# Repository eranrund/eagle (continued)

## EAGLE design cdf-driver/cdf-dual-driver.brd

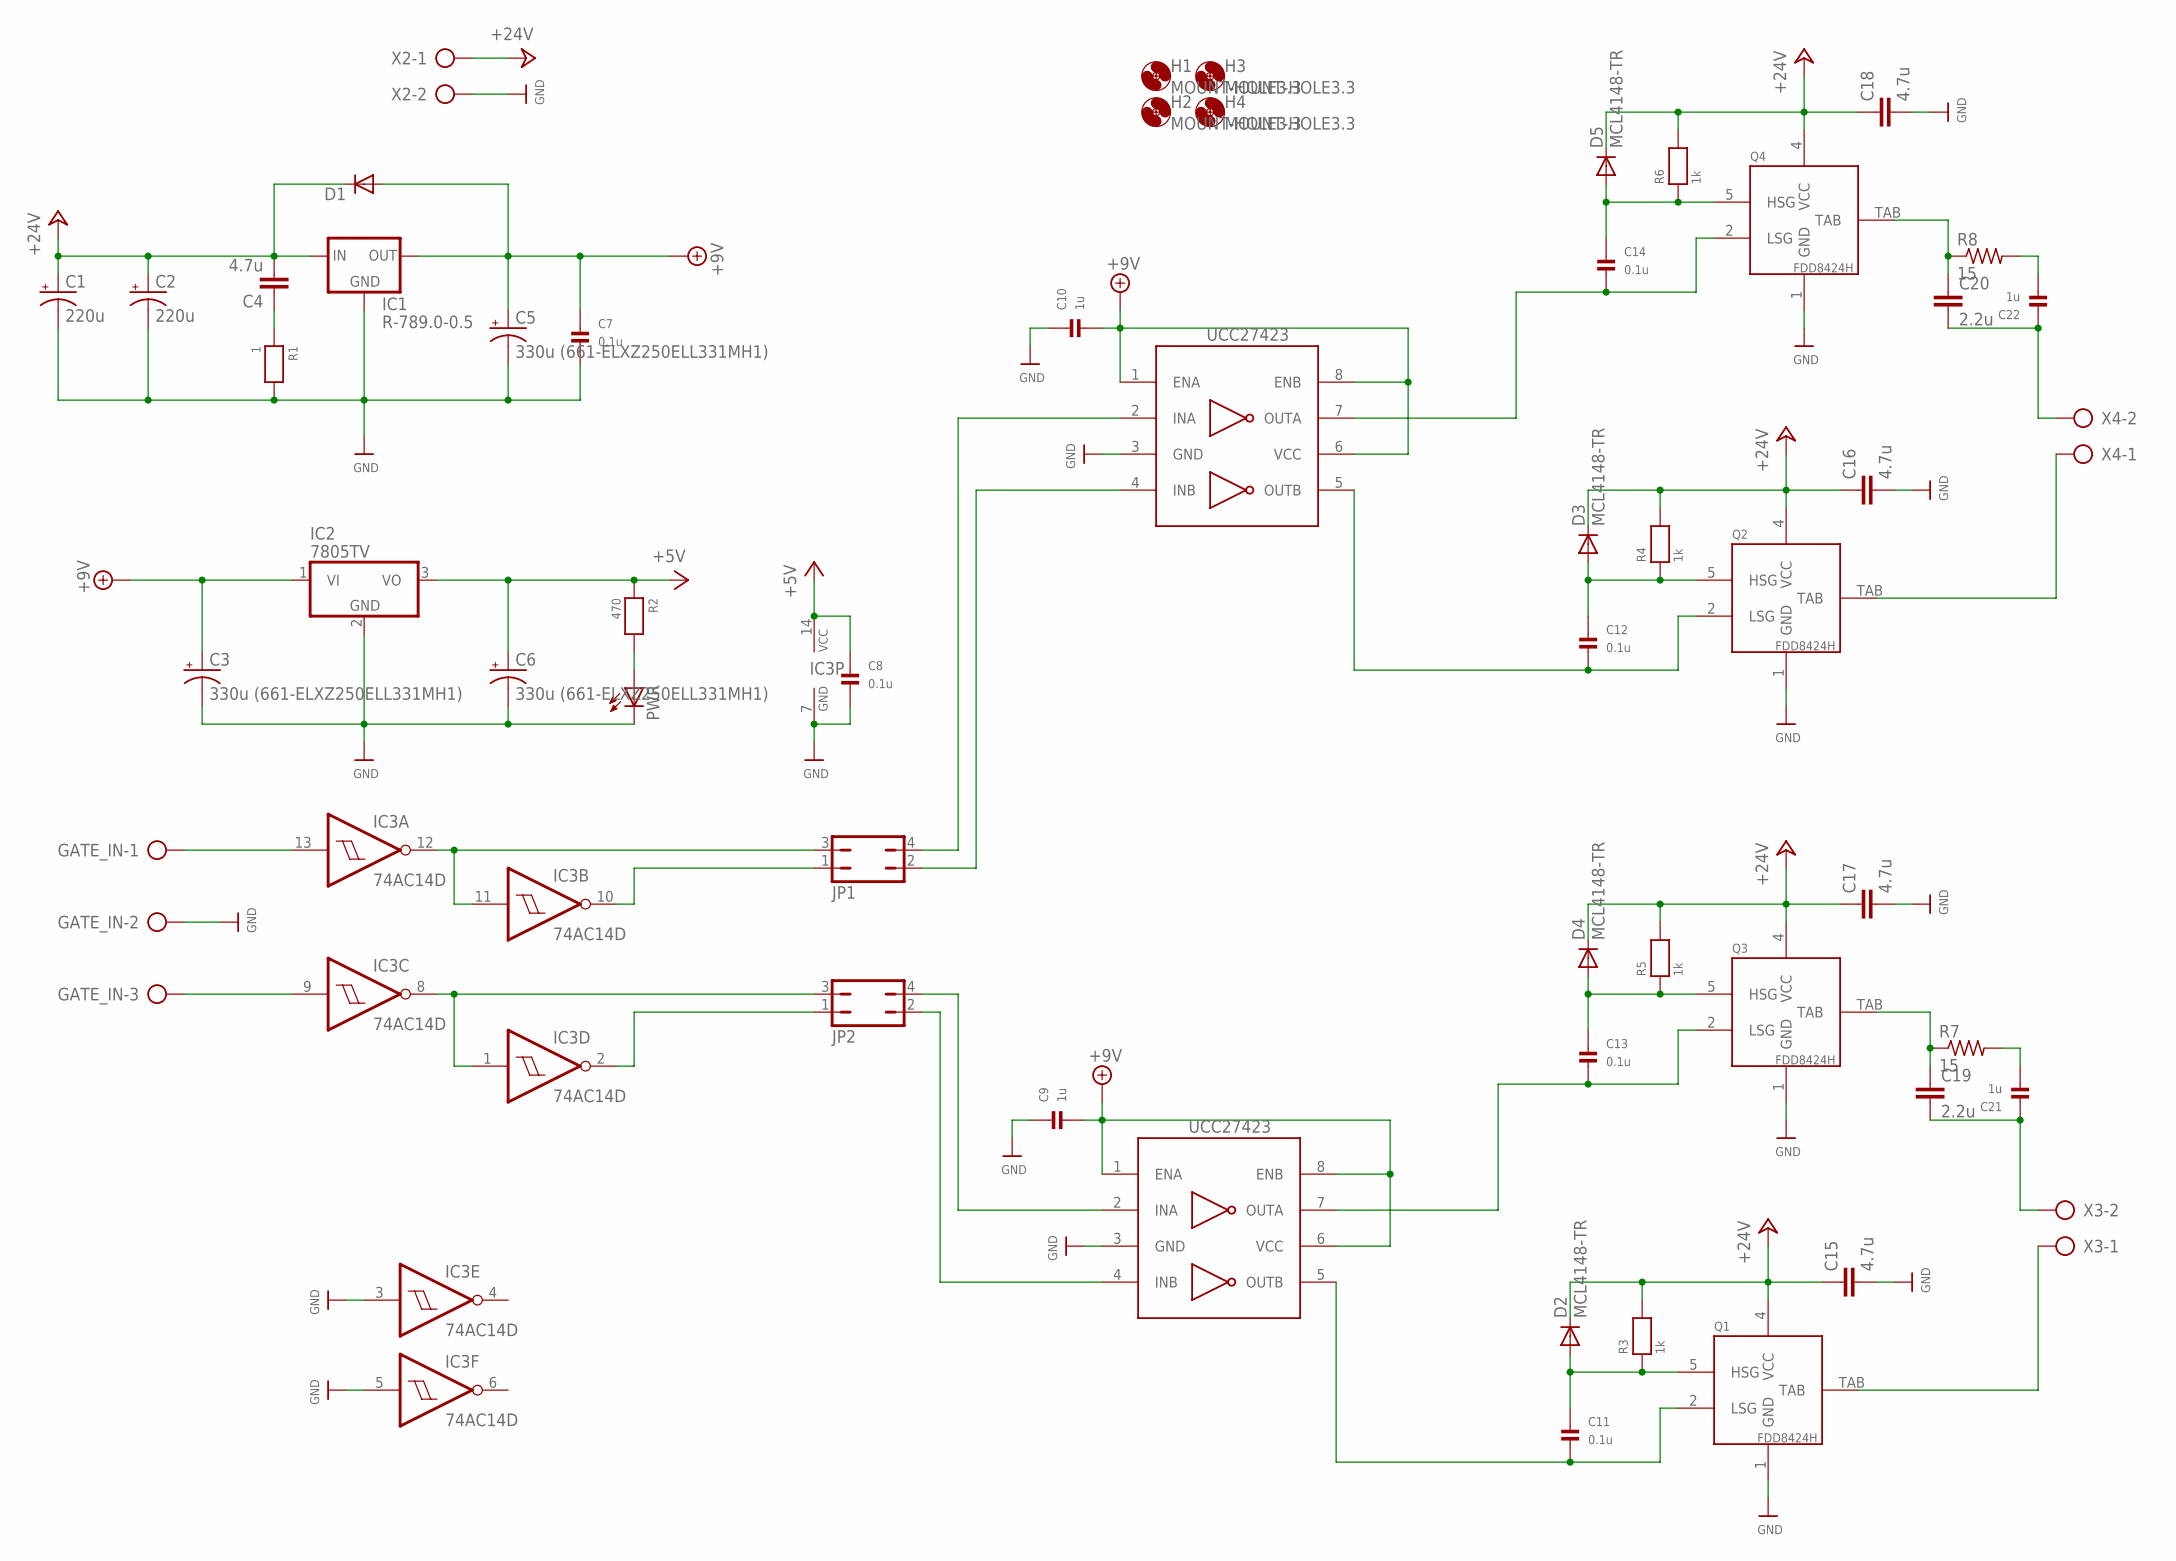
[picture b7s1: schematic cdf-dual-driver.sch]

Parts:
C1, C2: 220u; E3,5-8
C3, C5, C6: 330u (661-ELXZ250ELL331MH1); E3,5-8
C4, C15, C16, C17, C18: 4.7u; C1210
C7, C8, C11, C12, C13, C14: 0.1u; 0805
C9, C10, C21, C22: 1u; 1206
C19, C20: 2.2u; C1210
D1: DIODE-SOD123; SOD123
D2, D3, D4, D5: MCL4148-TR; MICROMELF-W
GATE_IN: AK500/3
H1, H2, H3, H4: MOUNT-HOLE3.3; 3,3
IC1: R-789.0-0.5; SIP3
IC2: 7805TV; TO220V
IC3: 74AC14D; SO14
IC4, IC5: UCC27423; SOIC8
JP1, JP2: JP2Q
PWR: LED5MM
Q1, Q2, Q3, Q4: FDD8424H; TO252-4
R1: 1; 0805
R2: 470; 0805
R3, R4, R5, R6: 1k; 0805
R7, R8: 15; R1210
X2, X3, X4: AK500/2

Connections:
+5V: C6.+, C8.1, IC2.3 (VO), IC3.14 (VCC), R2.1
+9V: C3.+, C5.+, C7.1, C9.2, C10.2, D1.A, IC1.3 (OUT), IC2.1 (VI), IC4.1 (ENA), IC4.6 (VCC), IC4.8 (ENB), IC5.1 (ENA), IC5.6 (VCC), IC5.8 (ENB)
+24V: C1.+, C2.+, C4.2, C15.1, C16.1, C17.1, C18.1, D1.C, D2.C, D3.C, D4.C, D5.C, IC1.1 (IN), Q1.4 (VCC), Q2.4 (VCC), Q3.4 (VCC), Q4.4 (VCC), R3.2, R4.2, R5.2, R6.2, X2.1
GND: C1.-, C2.-, C3.-, C5.-, C6.-, C7.2, C8.2, C9.1, C10.1, C15.2, C16.2, C17.2, C18.2, GATE_IN.2, IC1.2 (GND), IC2.2 (GND), IC3.3 (I), IC3.5 (I), IC3.7 (GND), IC4.3 (GND), IC5.3 (GND), PWR.K (C), Q1.1 (GND), Q2.1 (GND), Q3.1 (GND), Q4.1 (GND), R1.2, X2.2
unnamed: C13.2, IC4.7 (OUTA), Q3.2 (LSG)
unnamed: C13.1, D4.A, Q3.5 (HSG), R5.1
unnamed: C14.2, IC5.7 (OUTA), Q4.2 (LSG)
unnamed: C14.1, D5.A, Q4.5 (HSG), R6.1
unnamed: C20.1, Q4.TAB, R8.1
unnamed: C22.2, R8.2
unnamed: C20.2, C22.1, X4.2
unnamed: C12.2, IC5.5 (OUTB), Q2.2 (LSG)
unnamed: C12.1, D3.A, Q2.5 (HSG), R4.1
unnamed: Q2.TAB, X4.1
unnamed: C4.1, R1.1
unnamed: C19.1, Q3.TAB, R7.1
unnamed: C21.2, R7.2
unnamed: C19.2, C21.1, X3.2
unnamed: C11.2, IC4.5 (OUTB), Q1.2 (LSG)
unnamed: C11.1, D2.A, Q1.5 (HSG), R3.1
unnamed: Q1.TAB, X3.1
unnamed: PWR.A, R2.2
unnamed: IC5.2 (INA), JP1.4
unnamed: IC5.4 (INB), JP1.2
unnamed: IC4.2 (INA), JP2.4
unnamed: IC4.4 (INB), JP2.2
unnamed: IC3.11 (I), IC3.12 (O), JP1.3
unnamed: GATE_IN.1, IC3.13 (I)
unnamed: GATE_IN.3, IC3.9 (I)
unnamed: IC3.10 (O), JP1.1
unnamed: IC3.1 (I), IC3.8 (O), JP2.3
unnamed: IC3.2 (O), JP2.1

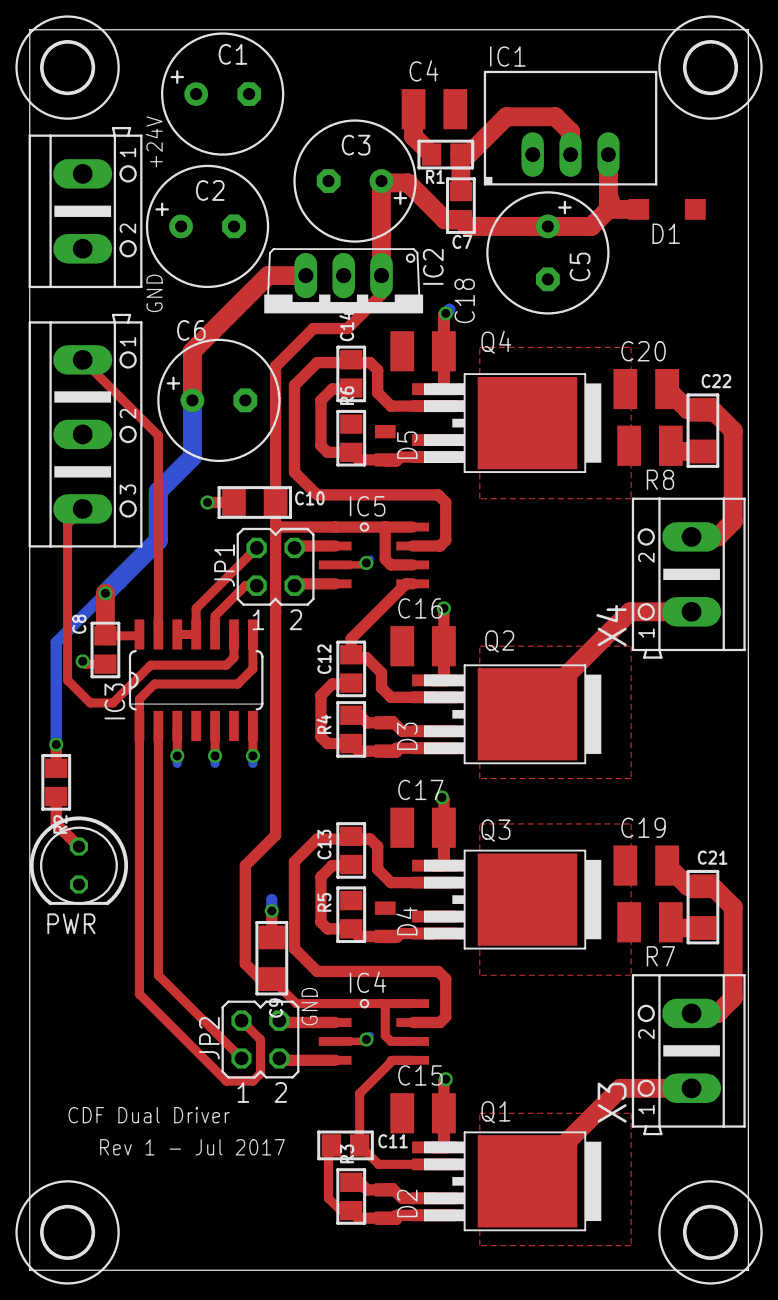
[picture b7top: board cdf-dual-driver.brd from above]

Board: 2 copper layers, 48.3 x 83.3 mm, 55 parts (0 on the bottom side), 32 nets.

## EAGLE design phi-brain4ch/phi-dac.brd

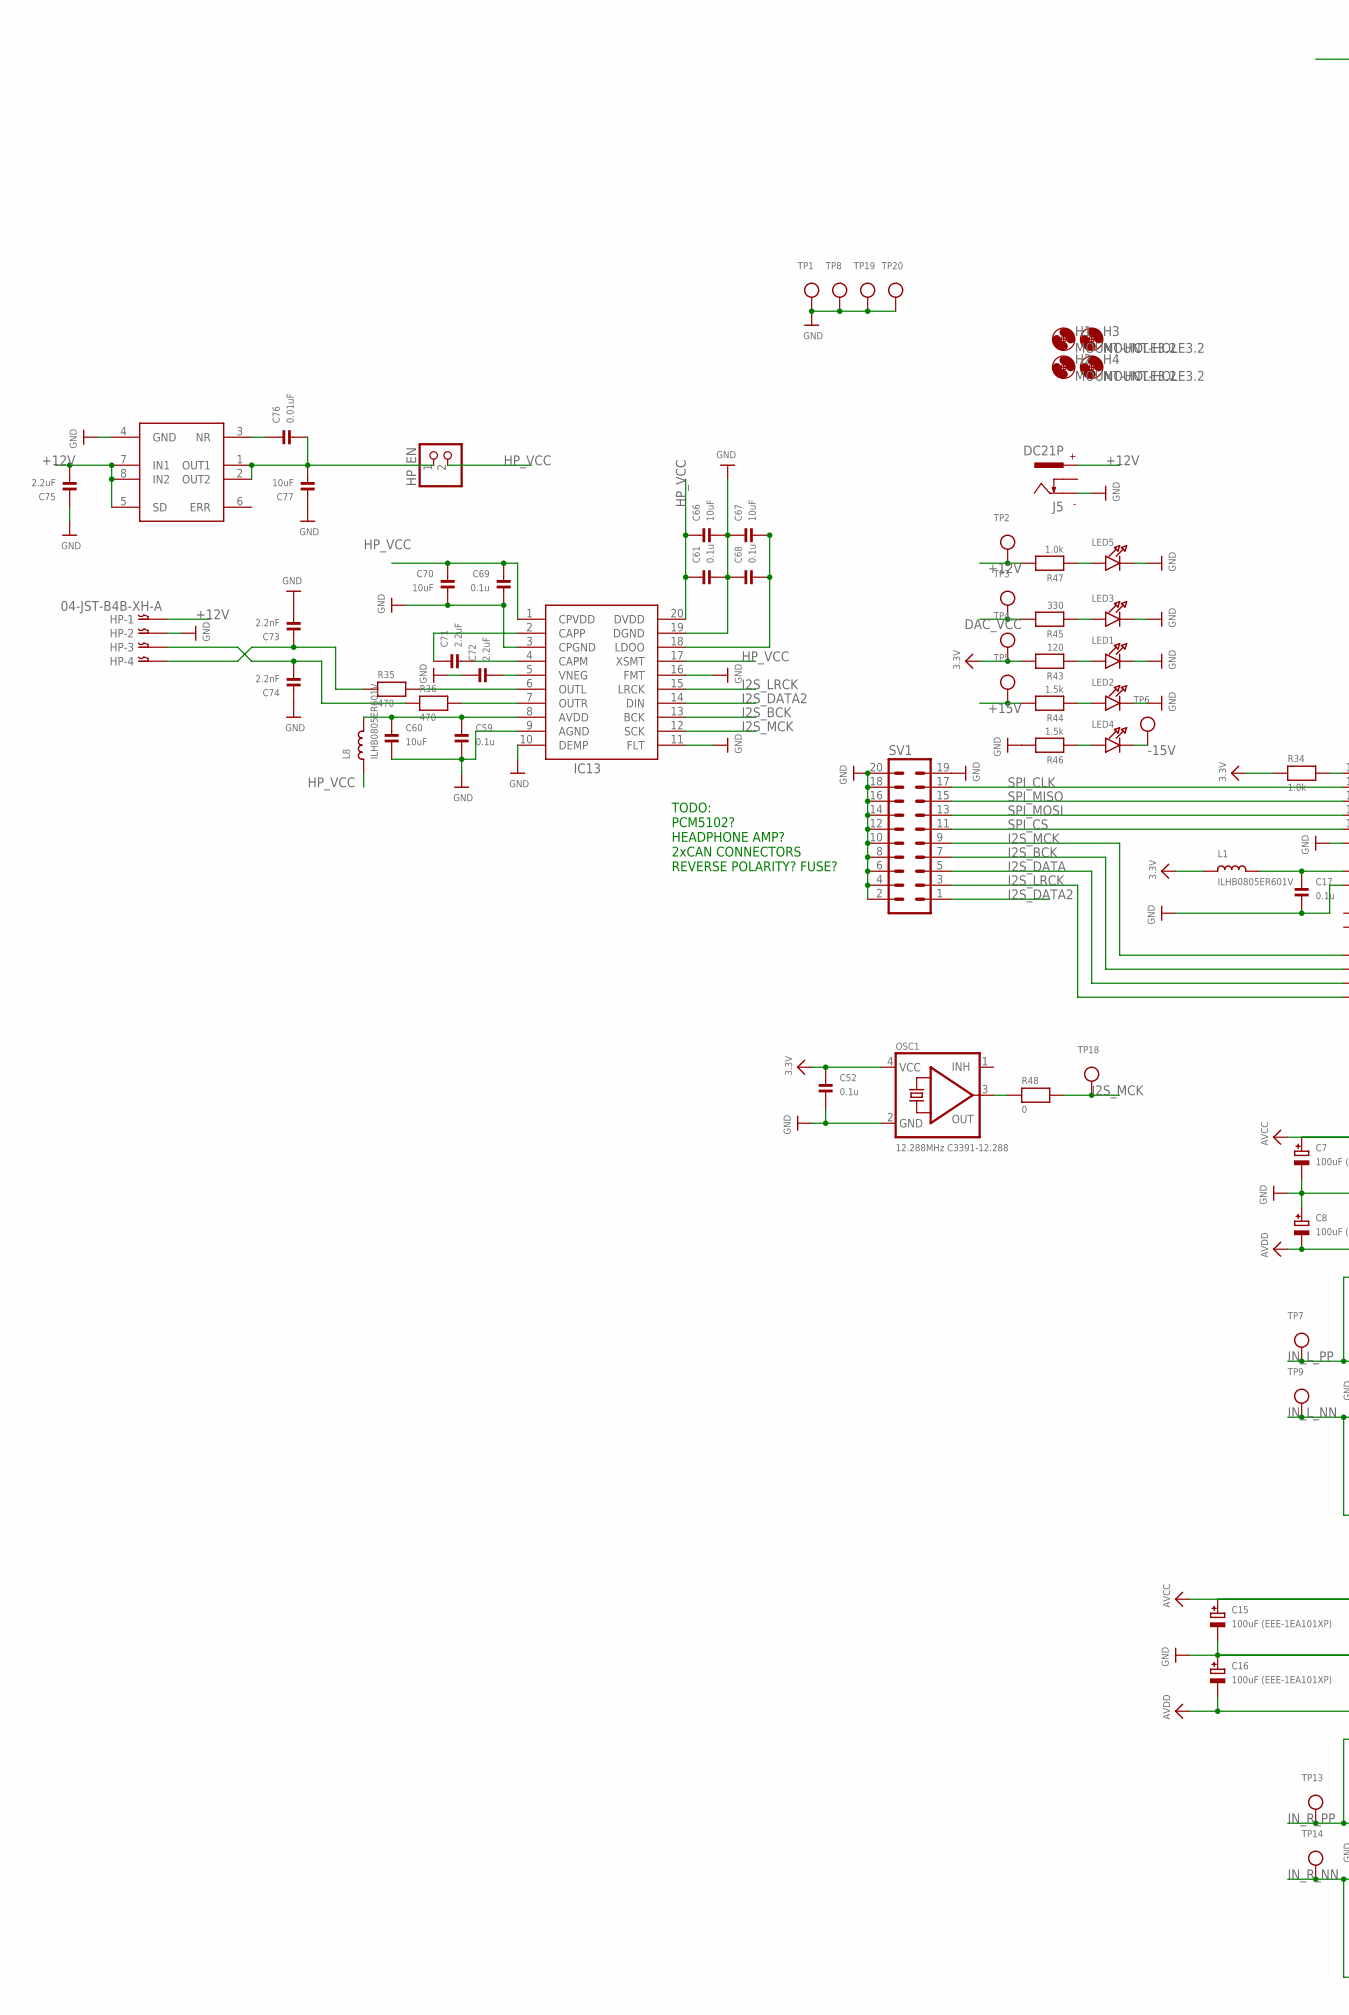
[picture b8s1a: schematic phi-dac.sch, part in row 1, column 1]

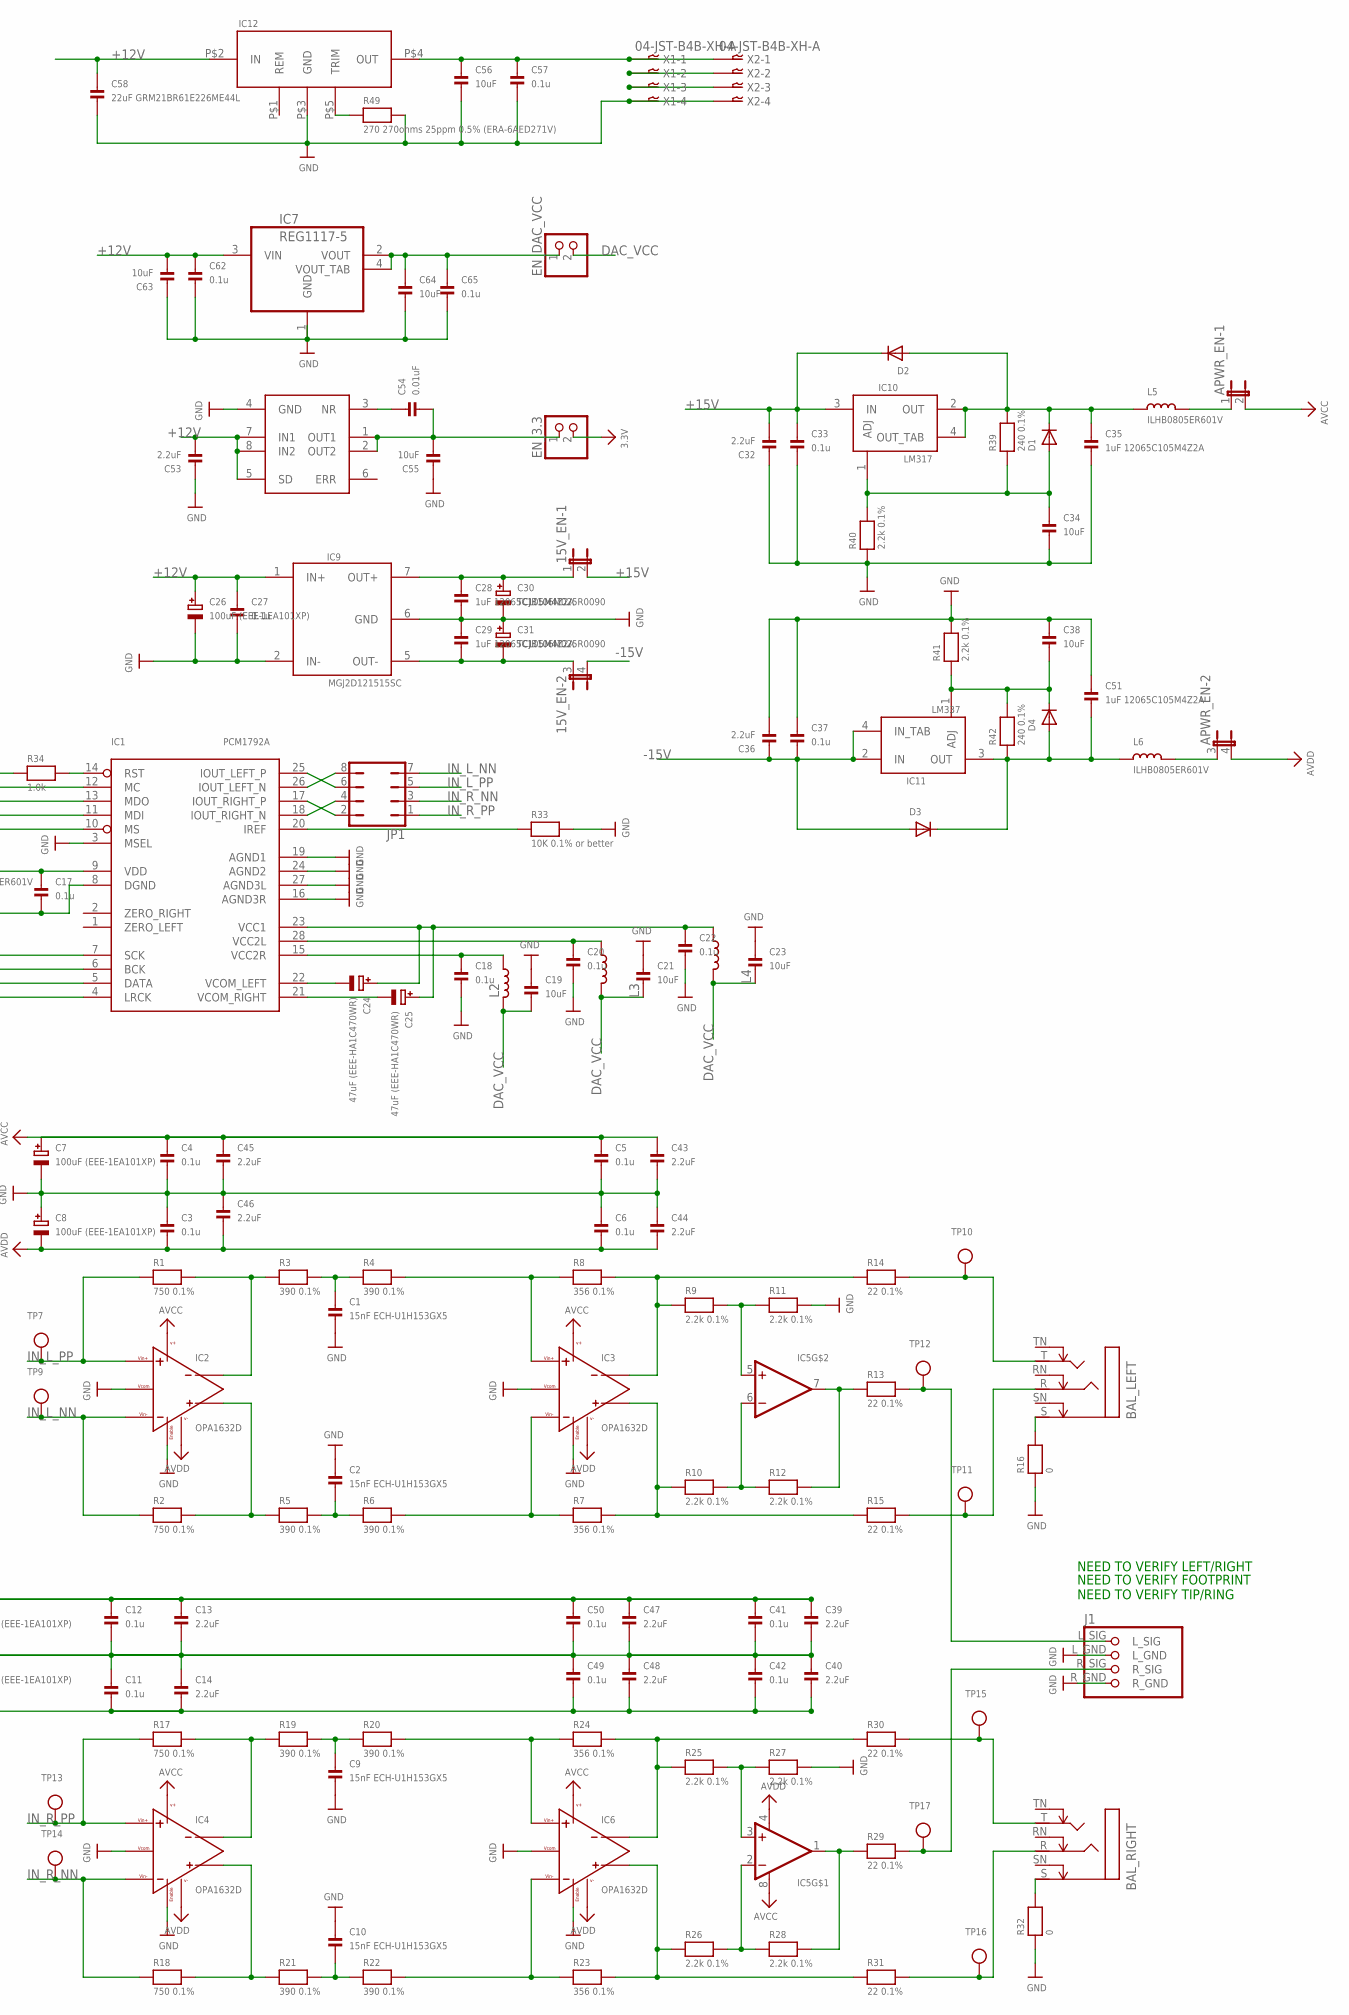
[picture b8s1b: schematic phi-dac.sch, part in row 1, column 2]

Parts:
15V_EN: JP2QE; JP2Q
APWR_EN: JP2QE; JP2Q
BAL_LEFT: STEREOSW; NMJ6HCD2
BAL_RIGHT: STEREOSW; NMJ6HCD2
C1, C2, C9, C10: 15nF ECH-U1H153GX5; 1210
C3, C4, C5, C6, C11, C12, C17, C18, C20, C22, C27, C33, C37, C41, C42, C49, C50, C52, C57, C59, C61, C62, C65, C68, C69: 0.1u; 0603
C7, C8, C15, C16, C26: 100uF (EEE-1EA101XP); PANASONIC_D
C13, C14, C32, C36, C39, C40, C43, C44, C45, C46, C47, C48, C53, C71, C72, C75: 2.2uF; _0805
C19, C21, C23, C34, C38, C55, C56, C60, C63, C64, C66, C67, C70, C77: 10uF; 0805
C24, C25: 47uF (EEE-HA1C470WR); PANASONIC_C
C28, C29, C35, C51: 1uF 12065C105M4Z2A; 1206
C30, C31: TCJB106M025R0090; 1210POL
C54, C76: 0.01uF; 0603
C58: 22uF GRM21BR61E226ME44L; _0805
C73, C74: 2.2nF; _0805
D1, D2, D3, D4: DIODESOD-123; SOD-123
EN_3.3: HEADER-1X2; 1X02_OVAL
EN_DAC_VCC: HEADER-1X2; 1X02_OVAL
H1, H2, H3, H4: MOUNT-HOLE3.2; 3,2
HP: 04-JST-B4B-XH-A; B4B-XH
HP_EN: HEADER-1X2; 1X02_OVAL
IC1: PCM1792A; SSOP28
IC2, IC3, IC4, IC6: OPA1632D; SO08
IC5: LM4562; SOIC8_150MIL
IC7: REG1117-5; SOT223
IC8, IC14: ADP3301ARZ-3.3; SO08
IC9: MGJ2D121515SC; MURATA-MGJ2
IC10: LM317; SOT223
IC11: LM337; SOT223
IC12: MURATA_OKR-T/10-W12-C
IC13: PCM5102; TSSOP20
J1: CUI-RCJ-2123
J5: DC21P; CUI-PJ-102AH
JP1: JP4Q
L1, L2, L3, L4, L5, L6, L8: ILHB0805ER601V; _0805
LED1, LED2, LED3, LED4, LED5: LED0805; CHIPLED_0805
OSC1: 12.288MHz C3391-12.288; OSC_7X5MM
R1, R2, R17, R18: 750 0.1%; _0805
R3, R4, R5, R6, R19, R20, R21, R22: 390 0.1%; _0805
R7, R8, R23, R24: 356 0.1%; _0805
R9, R10, R11, R12, R25, R26, R27, R28, R40, R41: 2.2k 0.1%; _0805
R13, R14, R15, R29, R30, R31: 22 0.1%; _0805
R16, R32, R48: 0; _0805
R33: 10K 0.1% or better; _0805
R34, R47: 1.0k; _0805
R35, R36: 470; _0805
R39, R42: 240 0.1%; _0805
R43: 120; _0805
R44, R46: 1.5k; _0805
R45: 330; _0805
R49: 270 270ohms 25ppm 0.5% (ERA-6AED271V); _0805
SV1: ML20
TP1, TP2, TP3, TP4, TP5, TP6, TP7, TP8, TP9, TP10, TP11, TP12, TP13, TP14, TP15, TP16, TP17, TP18, TP19, TP20: TESTPOINT0.1"; 1X01_ROUND
X1, X2: 04-JST-B4B-XH-A; B4B-XH

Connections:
3.3V: C52.1, EN_3.3.2, L1.1, OSC1.4 (VCC), R34.1, R43.2, TP4.1
+12V: C26.+, C27.1, C53.2, C58.1, C62.1, C63.2, C75.2, HP.P$1, IC7.3 (VIN), IC8.5 (SD), IC8.7 (IN1), IC8.8 (IN2), IC9.1 (IN+), IC12.P$2 (IN), IC14.5 (SD), IC14.7 (IN1), IC14.8 (IN2), J5.+, R47.2, TP2.1
+15V: 15V_EN.2, C32.2, C33.1, D2.C, IC10.3 (IN), R44.2, TP5.1
-15V: 15V_EN.4 (2), C36.1, C37.2, D3.A, IC11.2 (IN), IC11.4 (IN_TAB), LED4.C, TP6.1
AVCC: APWR_EN.2, C4.1, C5.1, C7.+, C12.1, C13.1, C15.+, C39.1, C41.1, C43.1, C45.1, C47.1, C50.1, IC2.3 (V+), IC3.3 (V+), IC4.3 (V+), IC5.8 (V+), IC6.3 (V+)
AVDD: APWR_EN.4 (2), C3.2, C6.2, C8.-, C11.2, C14.2, C16.-, C40.2, C42.2, C44.2, C46.2, C48.2, C49.2, IC2.6 (V-), IC3.6 (V-), IC4.6 (V-), IC5.4 (V-), IC6.6 (V-)
CAN_H: X1.P$3, X2.P$3
CAN_L: X1.P$2, X2.P$2
DAC_VCC: C19.2, C21.2, C23.2, EN_DAC_VCC.2, L2.2, L3.2, L4.2, R45.2, TP3.1
GND: C1.2, C2.1, C3.1, C4.2, C5.2, C6.1, C7.-, C8.+, C9.2, C10.1, C11.1, C12.2, C13.2, C14.1, C15.-, C16.+, C17.2, C18.2, C19.1, C20.2, C21.1, C22.2, C23.1, C26.-, C27.2, C28.2, C29.1, C30.2- (-), C31.1+ (+), C32.1, C33.2, C34.2, C35.2, C36.2, C37.1, C38.1, C39.2, C40.1, C41.2, C42.1, C43.2, C44.1, C45.2, C46.1, C47.2, C48.1, C49.1, C50.2, C51.1, C52.2, C53.1, C55.1, C56.2, C57.2, C58.2, C59.2, C60.2, C61.2, C62.2, C63.1, C64.2, C65.2, C66.2, C67.1, C68.1, C69.2, C70.2, C72.1, C73.2, C74.1, C75.1, C77.1, HP.P$2, IC1.3 (MSEL), IC1.8 (DGND), IC1.16 (AGND3R), IC1.19 (AGND1), IC1.24 (AGND2), IC1.27 (AGND3L), IC2.2 (VCOM), IC2.7 (ENABLE), IC3.2 (VCOM), IC3.7 (ENABLE), IC4.2 (VCOM), IC4.7 (ENABLE), IC6.2 (VCOM), IC6.7 (ENABLE), IC7.1 (GND), IC8.4 (GND), IC9.2 (IN-), IC9.6 (GND), IC12.P$3 (GND), IC13.3 (CPGND), IC13.9 (AGND), IC13.10 (DEMP), IC13.11 (FLT), IC13.16 (FMT), IC13.19 (DGND), IC14.4 (GND), J1.L_GND, J1.R_GND, J5.-, LED1.C, LED2.C, LED3.C, LED5.C, OSC1.2 (GND), R11.2, R16.1, R27.2, R32.1, R33.2, R40.1, R41.2, R46.2, R49.2, SV1.2, SV1.4, SV1.6, SV1.8, SV1.10, SV1.12, SV1.14, SV1.16, SV1.18, SV1.19, SV1.20, TP1.1, TP8.1, TP19.1, TP20.1, X1.P$4, X2.P$4
HP_L_OUT: C73.1, HP.P$4, R35.1
HP_R_OUT: C74.2, HP.P$3, R36.1
HP_VCC: C61.1, C66.1, C69.1, C70.1, HP_EN.2, IC13.1 (CPVDD), IC13.17 (XSMT), IC13.20 (DVDD), L8.1
I2S_BCK: IC1.6 (BCK), IC13.13 (BCK), SV1.7
I2S_DATA: IC1.5 (DATA), SV1.5
I2S_DATA2: IC13.14 (DIN), SV1.1
I2S_LRCK: IC1.4 (LRCK), IC13.15 (LRCK), SV1.3
I2S_MCK: IC1.7 (SCK), IC13.12 (SCK), R48.2, SV1.9, TP18.1
IN_L_NN: IC2.1 (VIN-), JP1.7, R2.1, TP9.1
IN_L_PP: IC2.8 (VIN+), JP1.5, R1.1, TP7.1
IN_R_NN: IC4.1 (VIN-), JP1.3, R18.1, TP14.1
IN_R_PP: IC4.8 (VIN+), JP1.1, R17.1, TP13.1
unnamed: IC2.5 (VOUT-), R1.2, R3.1
unnamed: IC2.4 (VOUT+), R2.2, R5.1
unnamed: C1.1, R3.2, R4.1
unnamed: C2.2, R5.2, R6.1
unnamed: IC3.8 (VIN+), R4.2, R8.1
unnamed: IC3.1 (VIN-), R6.2, R7.1
unnamed: IC1.17 (IOUT_RIGHT_P), JP1.2
unnamed: IC1.18 (IOUT_RIGHT_N), JP1.4
unnamed: IC5.5 (+IN), R9.2, R11.1
unnamed: IC5.6 (-IN), R10.2, R12.1
unnamed: IC5.7 (OUT), R12.2, R13.1
unnamed: J1.L_SIG, R13.2, TP12.1
unnamed: BAL_LEFT.S, R16.2
unnamed: BAL_LEFT.T, R14.2, TP10.1
unnamed: BAL_LEFT.R, R15.2, TP11.1
unnamed: IC4.5 (VOUT-), R17.2, R19.1
unnamed: IC4.4 (VOUT+), R18.2, R21.1
unnamed: C9.1, R19.2, R20.1
unnamed: C10.2, R21.2, R22.1
unnamed: IC6.8 (VIN+), R20.2, R24.1
unnamed: IC6.1 (VIN-), R22.2, R23.1
unnamed: IC1.26 (IOUT_LEFT_N), JP1.8
unnamed: IC1.25 (IOUT_LEFT_P), JP1.6
unnamed: IC5.3 (+IN), R25.2, R27.1
unnamed: IC5.2 (-IN), R26.2, R28.1
unnamed: J1.R_SIG, R29.2, TP17.1
unnamed: BAL_RIGHT.S, R32.2
unnamed: BAL_RIGHT.T, R30.2, TP15.1
unnamed: BAL_RIGHT.R, R31.2, TP16.1
unnamed: C56.1, C57.1, IC12.P$4 (OUT), X1.P$1, X2.P$1
unnamed: OSC1.3 (OUT), R48.1
unnamed: IC12.P$5 (TRIM), R49.1
unnamed: IC5.1 (OUT), R28.2, R29.1
unnamed: IC1.20 (IREF), R33.1
unnamed: C18.1, IC1.15 (VCC2R), L2.1
unnamed: C17.1, IC1.9 (VDD), L1.2
unnamed: C20.1, IC1.28 (VCC2L), L3.1
unnamed: C22.1, C24.+, C25.+, IC1.23 (VCC1), L4.1
unnamed: C24.-, IC1.22 (VCOM_LEFT)
unnamed: C25.-, IC1.21 (VCOM_RIGHT)
unnamed: IC1.14 (RST), R34.2
unnamed: C59.1, C60.1, IC13.8 (AVDD), L8.2
unnamed: C67.2, C68.2, IC13.18 (LDOO)
unnamed: C71.1, IC13.2 (CAPP)
unnamed: C54.2, C55.2, EN_3.3.1, IC8.1 (OUT1), IC8.2 (OUT2)
unnamed: C54.1, IC8.3 (NR)
unnamed: 15V_EN.3 (1), C29.2, C31.2- (-), IC9.5 (OUT-)
unnamed: 15V_EN.1, C28.1, C30.1+ (+), IC9.7 (OUT+)
unnamed: C64.1, C65.1, EN_DAC_VCC.1, IC7.2 (VOUT), IC7.4 (VOUT_TAB)
unnamed: APWR_EN.1, L5.2
unnamed: C35.1, D1.C, D2.A, IC10.2 (OUT), IC10.4 (OUT_TAB), L5.1, R39.2
unnamed: C34.1, D1.A, IC10.1 (ADJ), R39.1, R40.2
unnamed: APWR_EN.3 (1), L6.2
unnamed: LED1.A, R43.1
unnamed: C51.2, D3.C, D4.A, IC11.3 (OUT), L6.1, R42.1
unnamed: C38.2, D4.C, IC11.1 (ADJ), R41.1, R42.2
unnamed: LED3.A, R45.1
unnamed: LED2.A, R44.1
unnamed: LED4.A, R46.1
unnamed: LED5.A, R47.1
unnamed: C71.2, IC13.4 (CAPM)
unnamed: C72.2, IC13.5 (VNEG)
unnamed: C76.1, IC14.3 (NR)
unnamed: IC13.6 (OUTL), R35.2
unnamed: IC13.7 (OUTR), R36.2
unnamed: C76.2, C77.2, HP_EN.1, IC14.1 (OUT1), IC14.2 (OUT2)
OUT_L_NN: IC3.4 (VOUT+), R7.2, R10.1, R15.1
OUT_L_PP: IC3.5 (VOUT-), R8.2, R9.1, R14.1
OUT_R_NN: IC6.4 (VOUT+), R23.2, R26.1, R31.1
OUT_R_PP: IC6.5 (VOUT-), R24.2, R25.1, R30.1
SPI_CLK: IC1.12 (MC), SV1.17
SPI_CS: IC1.10 (MS), SV1.11
SPI_MISO: IC1.13 (MDO), SV1.15
SPI_MOSI: IC1.11 (MDI), SV1.13

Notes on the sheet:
NEED TO VERIFY FOOTPRINT NEED TO VERIFY TIP/RING
NEED TO VERIFY LEFT/RIGHT
TODO: PCM5102? HEADPHONE AMP? 2xCAN CONNECTORS REVERSE POLARITY? FUSE?

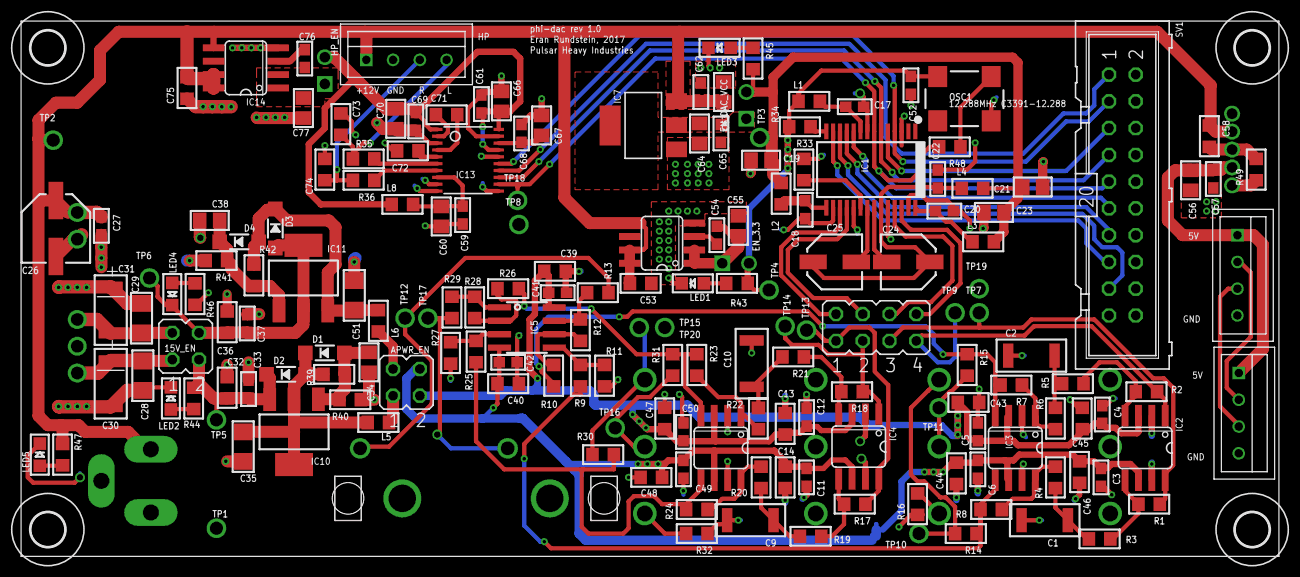
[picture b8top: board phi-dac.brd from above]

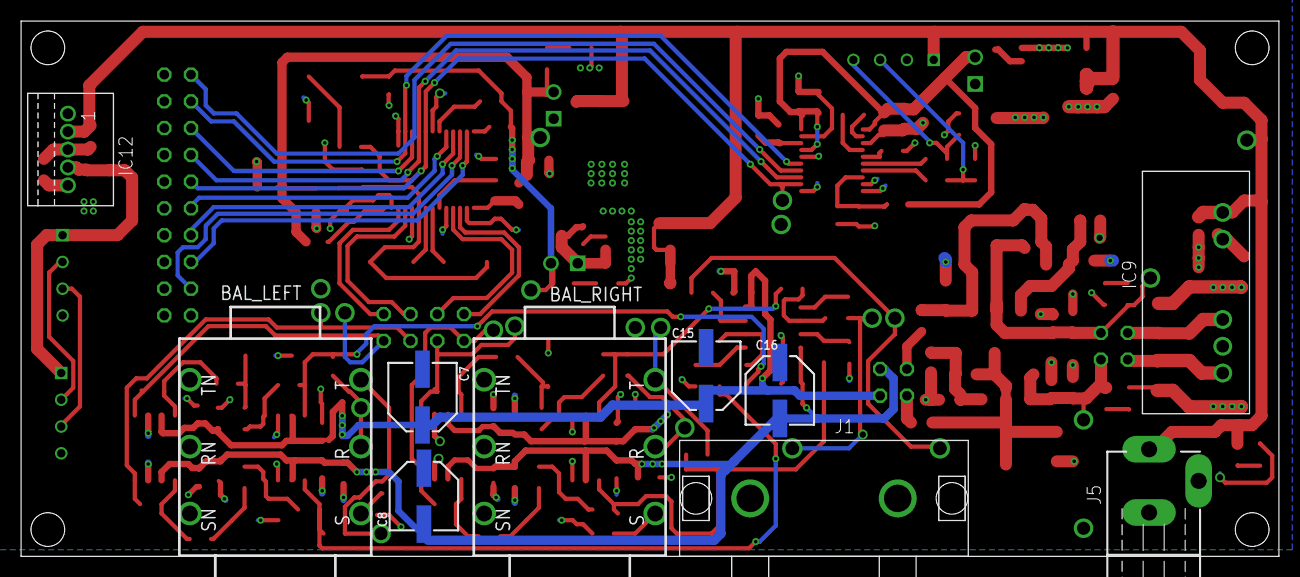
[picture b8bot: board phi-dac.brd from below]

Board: 2 copper layers, 119.4 x 50.8 mm, 193 parts (10 on the bottom side), 96 nets.

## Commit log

2016-06-27 LedKeychain
2016-07-13 bah macbooks
2016-07-13 fade
2016-07-13 buttonsssss
2016-07-23 interrupter
2016-07-26 cdf interrupter sent to fab
2016-08-12 led-keychain eeprom + weird behavior
2016-08-12 disable serial
2016-09-18 reviving midimixer
2016-09-20 midimixer-st-eval
2016-10-10 add macrofab files
2016-10-11 ab-berry
2016-10-13 ab-berry: added xtal :/
2016-10-13 ab-berry: silkscreen
2016-10-21 add pushbutton
2016-10-26 fix can tx<->rx (flip them)
2016-10-28 seeedstudio
2016-10-29 ab-berry: add rc filter network to rotencs
2016-10-29 ab-berry: small layout cleanup
2016-10-29 ab-berry: switch tantalum caps footprint
2016-10-31 midimixer-channel: switch pots to available ones, switch ssd1306 to 7 pin
2016-11-22 add x0x heart
2016-11-25 pl-jacks
2016-11-25 dac wip
2016-12-03 compressor
2016-12-10 midimixer channel fixes post ab-berry
2016-12-10 midimixer-channel encoder rework
2016-12-14 remove ab-main-mini attempt, add footprint for STM32F302RC
2016-12-15 switch ab-berry-rev2 to STM32F303CCT6
2016-12-17 make ab-berry-rev2 pass oshpask drc
2016-12-19 midimixer-channel wip
2017-01-13 ab-berry-rev 2.1 wip
2017-01-15 ab-berry rev2.1 sent to macrofab
2017-01-16 midimixer-channel rev a sent to macrofab
2017-02-17 ab-berry-rev2.2: added transistor+pullup for USB, renumbered sheet
2017-02-17 add prefixes
2017-02-21 dac-eval-simplifed: minimized
2017-02-21 case
2017-02-27 compressor cleanups
2017-03-01 compressor: terminate opamps
2017-03-04 add noisebridge tested dual_ab-berry.ai
2017-03-04 change color mode
2017-03-04 small compressor changes
2017-03-04 misc ab-berry ai change
2017-03-04 first version of midimixer-channel.ai
2017-03-05 add notes
2017-03-06 ab-berry: master jumper, phi branding, some macrofab attribs
2017-03-07 ab-berry rev2-2 sent to macrofab
2017-03-08 midimixer-channel: change green led resistors, some other misc changes
2017-03-09 midimixer-channel-rev2 wip
2017-03-10 midimixer channel rev2 sent to macrofab
2017-03-21 cdf-modular-bridge rev B
2017-03-23 add st-tag-adapter
2017-03-25 relocate st-tag-adapter to phi repo
2017-03-25 add single_ab-berry.ai - UNTESTED
2017-03-28 add libs/micro-stm_v3.lbr
2017-03-28 ab-berry illustrator wip
2017-03-31 single and dual ab-berry lasercut!
2017-04-04 cdf-single-driver wip
2017-04-08 cdf-single-driver
2017-04-08 midimixer-channel/midimixer-channel-rev2.ai
2017-04-10 small cdf-single-driver changes
2017-04-10 midimixer-channel-rev2: illustrator file, change r8 and r15 to 200 ohm (blue leds too bright)
2017-04-17 add usb connector
2017-04-21 correct optical footprint
2017-04-21 cdf-teensy-interrupter-v2
2017-04-24 phi-brain4ch wip
2017-04-26 routed
2017-04-27 with headphone wip
2017-05-26 cdf stuff
2017-05-26 practice-board
2017-06-30 phi-brain4ch/phi-audio-standalone.ai lasecut successfully
2017-07-08 cdf-single-driver/ -> cdf-driver/
2017-10-26 bleh
2018-01-25 dual led wireless dimmer rev 2
2018-01-25 dual led wireless dimmer rev 2.1
2018-01-25 dual led wireless dimmer rev 2.2
2018-02-26 enclosure
2019-04-17 quad-wireless-switch rev a
2019-04-23 quad wireless switch wip
2019-04-30 quad wireless switch with nrf24
2019-05-27 quad-wireless-switch
2019-05-28 quad-wireless switch code update
2019-11-12 add stm32f446
2019-11-12 add cam file
2020-10-01 rotate
2020-12-04 dt rev b initial edit: remove jumpers, commit to i2c
2020-12-04 dt rev b: new layout wip
2021-02-12 dt rev b
